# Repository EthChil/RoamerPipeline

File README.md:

# RoamerPipeline

Custom pipeline designed to conduct SfM given an input of images gathered by hand or robotically.

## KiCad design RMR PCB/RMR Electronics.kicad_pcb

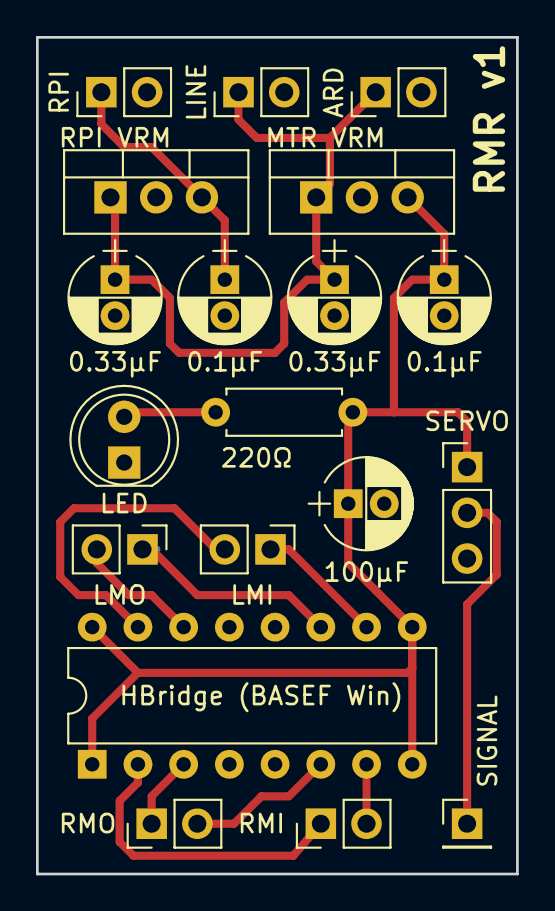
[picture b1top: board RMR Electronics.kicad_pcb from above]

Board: 2 copper layers, 26.7 x 46.5 mm, 19 parts (0 on the bottom side), 15 nets.

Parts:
0.1μF, 0.1μF#2: 0.1uf; CP_Radial_D5.0mm_P2.00mm
0.33μF, 0.33μF#2: 0.33uf; CP_Radial_D5.0mm_P2.00mm
100μF: 100 uf; CP_Radial_D5.0mm_P2.00mm
220Ω: 220; R_Axial_DIN0207_L6.3mm_D2.5mm_P7.62mm_Horizontal
ARD: Arduino Power; Pin_Header_Straight_1x02_Pitch2.54mm
HBridge (BASEF Win): HBridge; DIP-16_W7.62mm
LED: LED; LED_D5.0mm
LINE: Power In; Pin_Header_Straight_1x02_Pitch2.54mm
LMI: LMotor Control; Pin_Header_Straight_1x02_Pitch2.54mm
LMO: LMotor; Pin_Header_Straight_1x02_Pitch2.54mm
MTR VRM: AP2204R-5.0; TO-220-3_Vertical
RMI: RMotor Control; Pin_Header_Straight_1x02_Pitch2.54mm
RMO: RMotor; Pin_Header_Straight_1x02_Pitch2.54mm
RPI: RPI Power; Pin_Header_Straight_1x02_Pitch2.54mm
RPI VRM: RPI VRM; TO-220-3_Vertical
SERVO: Mast Servo; Pin_Header_Straight_1x03_Pitch2.54mm
SIGNAL: SIGNAL; Pin_Header_Straight_1x01_Pitch2.54mm

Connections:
GND: 0.1μF.2, 0.1μF#2.2, 0.33μF.2, 0.33μF#2.2, 100μF.2, ARD.2, HBridge (BASEF Win).4, HBridge (BASEF Win).5, HBridge (BASEF Win).12, HBridge (BASEF Win).13, LED.1, LINE.2, MTR VRM.2, RPI.2, RPI VRM.2, SERVO.3
unnamed: 0.33μF.1, 0.33μF#2.1, ARD.1, LINE.1, MTR VRM.1, RPI VRM.1
unnamed: 0.1μF.1, RPI.1, RPI VRM.3
unnamed: 0.1μF#2.1, 100μF.1, 220Ω.2, MTR VRM.3, SERVO.1
unnamed: HBridge (BASEF Win).1, HBridge (BASEF Win).8, HBridge (BASEF Win).9, HBridge (BASEF Win).16
unnamed: 220Ω.1, LED.2
unnamed: HBridge (BASEF Win).2, RMI.1
unnamed: HBridge (BASEF Win).3, RMO.1
unnamed: HBridge (BASEF Win).6, RMO.2
unnamed: HBridge (BASEF Win).7, RMI.2
unnamed: HBridge (BASEF Win).10, LMI.1
unnamed: HBridge (BASEF Win).11, LMO.1
unnamed: HBridge (BASEF Win).14, LMO.2
unnamed: HBridge (BASEF Win).15, LMI.2
unnamed: SERVO.2, SIGNAL.1

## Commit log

2018-06-01 Finished MVG pipeline
2018-06-01 added comment
2018-06-01 Added MVS and added extra failsafes
2018-06-01 general improvements
2018-06-02 Tested using plaza seems to work
2018-06-02 removed images
2018-06-02 properly organizes files
2018-06-02 updated after linux died
2018-06-02 Tested with Plaza
2018-06-05 Optimized MVG for maximum quality
2018-06-05 Created NACA Fomatter
2018-06-05 finished Naca parser
2018-06-05 front camber wing added
2018-06-05 normal glider profile added
2018-06-05 Thicc wing added
2018-06-08 KiCad Started
2018-06-09 V1 of the pcb design
2018-06-09 Modifications for the night
2018-07-04 Servo for Camera
    Arduino code for camera servo
2018-07-04 Finished layout
2018-07-04 added footprints
2018-07-05 assigned footprints
2018-07-05 modified battery power method
2018-07-05 started PCB layout
2018-07-06 reduced PCB size drastically, outstanding GND copper pour issue
2018-07-06 figured out that I am dumb
2018-07-06 logo
2018-07-06 cleaned up
2018-07-06 Fixed up an issue with the indicator LED
2018-07-06 Finalized logo and design
2018-07-07 exported
2018-07-09 removed unrelated parts
2018-09-30 Added RPI
2018-11-06 added tested firmata code
2018-11-07 ya boi
2018-11-07 added photo code
2018-11-08 updated pipeline
2018-11-08 Added rudimentary test code
2018-11-08 Tried to split the code
2018-11-08 cleaned and commented
2018-11-13 photoset
2018-11-13 added mac v linux path selection
2018-11-16 Updates to pipeline
2018-11-18 Pipeline updates
2018-12-18 added stl
2018-12-18 yees
2018-12-18 added gorman
2018-12-18 updated STL
2018-12-19 new ethan
2018-12-19 Added skate park shit
2018-12-19 Added plaza image set
2018-12-19 mesh
2018-12-20 Mapped Raymond
2018-12-20 Images and doctored Ray
2018-12-21 updated blend
2018-12-21 removed logs
2018-12-21 new Stl
2019-02-04 Added photo set
2019-02-04 fuck ya
2019-02-05 some stuff
2019-02-16 shit fam
